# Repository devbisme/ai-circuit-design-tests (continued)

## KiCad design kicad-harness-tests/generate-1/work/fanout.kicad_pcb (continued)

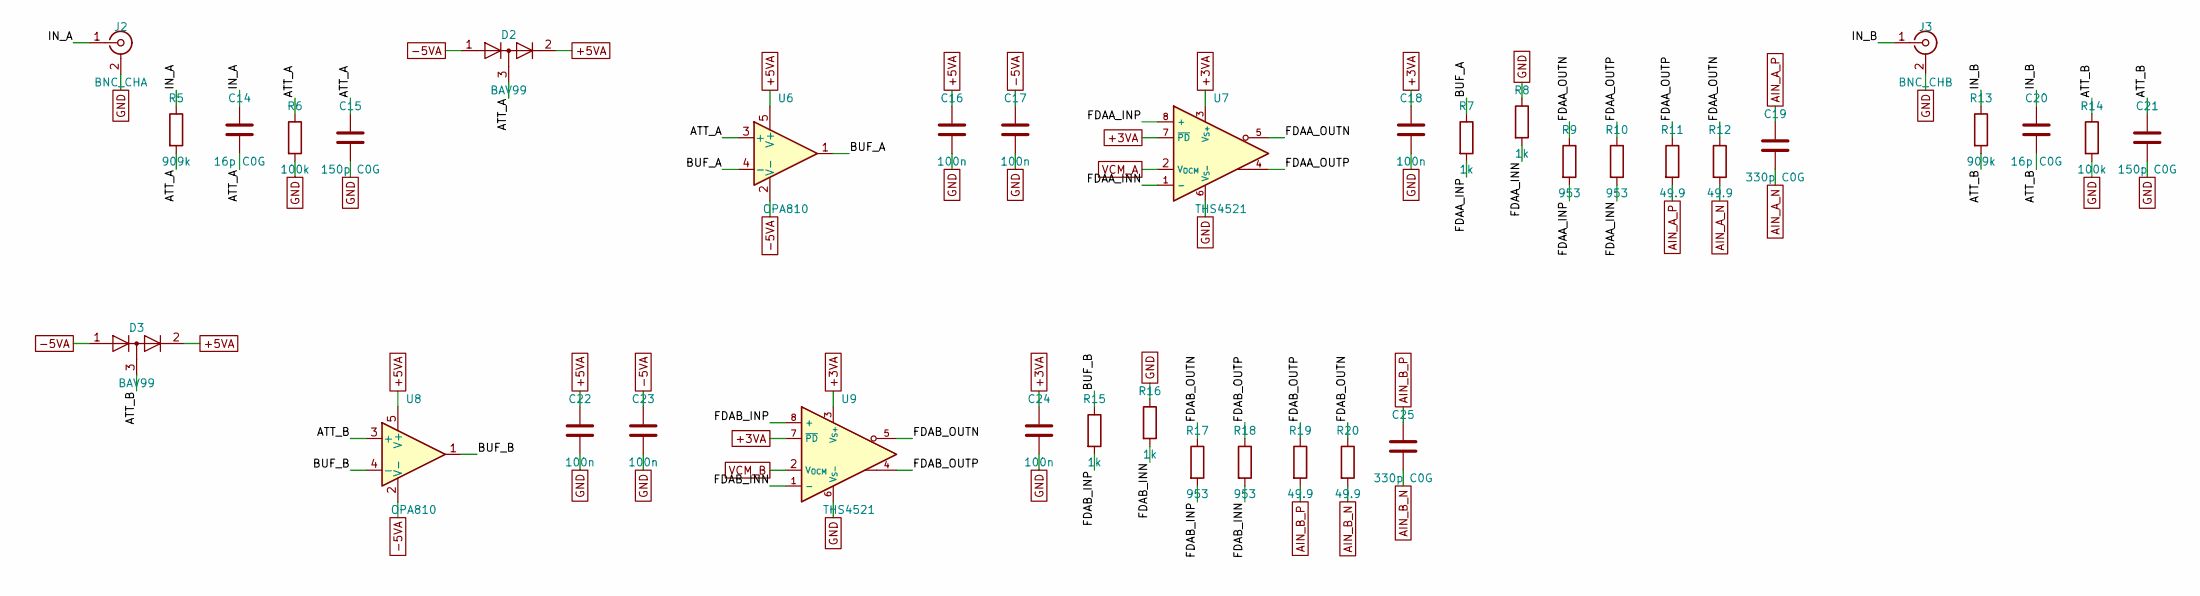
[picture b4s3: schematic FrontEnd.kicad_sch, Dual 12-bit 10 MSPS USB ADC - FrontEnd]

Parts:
C14, C20: 16p C0G; C_1206_3216Metric
C15, C21: 150p C0G; C_0603_1608Metric
C16, C17, C18, C22, C23, C24: 100n; C_0603_1608Metric
C19, C25: 330p C0G; C_0603_1608Metric
D2, D3: BAV99; SOT-23
J2: BNC_CHA; BNC_Amphenol_B6252HB-NPP3G-50_Horizontal
J3: BNC_CHB; BNC_Amphenol_B6252HB-NPP3G-50_Horizontal
R5, R13: 909k; R_1206_3216Metric
R6, R14: 100k; R_0603_1608Metric
R7, R8, R15, R16: 1k; R_0603_1608Metric
R9, R10, R17, R18: 953; R_0603_1608Metric
R11, R12, R19, R20: 49.9; R_0603_1608Metric
U6, U8: OPA810; SOT-23-5
U7, U9: THS4521; SOIC-8_3.9x4.9mm_P1.27mm

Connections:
+3VA: C18.1, C24.1, U7.3 (V_{S+}), U7.7 (~PD), U9.3 (V_{S+}), U9.7 (~PD); also elsewhere on the board
+5VA: C16.1, C22.1, D2.2 (A), D3.2 (A), U6.5 (V+), U8.5 (V+); also elsewhere on the board
-5VA: C17.1, C23.1, D2.1 (K), D3.1 (K), U6.2 (V-), U8.2 (V-); also elsewhere on the board
/FrontEnd/ATT_A: C14.2, C15.1, D2.3 (K), R5.2, R6.1, U6.3 (+)
/FrontEnd/ATT_B: C20.2, C21.1, D3.3 (K), R13.2, R14.1, U8.3 (+)
/FrontEnd/BUF_A: R7.1, U6.1, U6.4 (-)
/FrontEnd/BUF_B: R15.1, U8.1, U8.4 (-)
/FrontEnd/FDAA_INN: R8.2, R10.2, U7.1 (-)
/FrontEnd/FDAA_INP: R7.2, R9.2, U7.8 (+)
/FrontEnd/FDAA_OUTN: R9.1, R12.1, U7.5
/FrontEnd/FDAA_OUTP: R10.1, R11.1, U7.4
/FrontEnd/FDAB_INN: R16.2, R18.2, U9.1 (-)
/FrontEnd/FDAB_INP: R15.2, R17.2, U9.8 (+)
/FrontEnd/FDAB_OUTN: R17.1, R20.1, U9.5
/FrontEnd/FDAB_OUTP: R18.1, R19.1, U9.4
/FrontEnd/IN_A: C14.1, J2.1 (In), R5.1
/FrontEnd/IN_B: C20.1, J3.1 (In), R13.1
AIN_A_N: C19.2, R12.2; also elsewhere on the board
AIN_A_P: C19.1, R11.2; also elsewhere on the board
AIN_B_N: C25.2, R20.2; also elsewhere on the board
AIN_B_P: C25.1, R19.2; also elsewhere on the board
GND: C15.2, C16.2, C17.2, C18.2, C21.2, C22.2, C23.2, C24.2, J2.2 (Ext), J3.2 (Ext), R6.2, R8.1, R14.2, R16.1, U7.6 (V_{S-}), U9.6 (V_{S-}); also elsewhere on the board
VCM_A: U7.2 (V_{OCM}); also elsewhere on the board
VCM_B: U9.2 (V_{OCM}); also elsewhere on the board

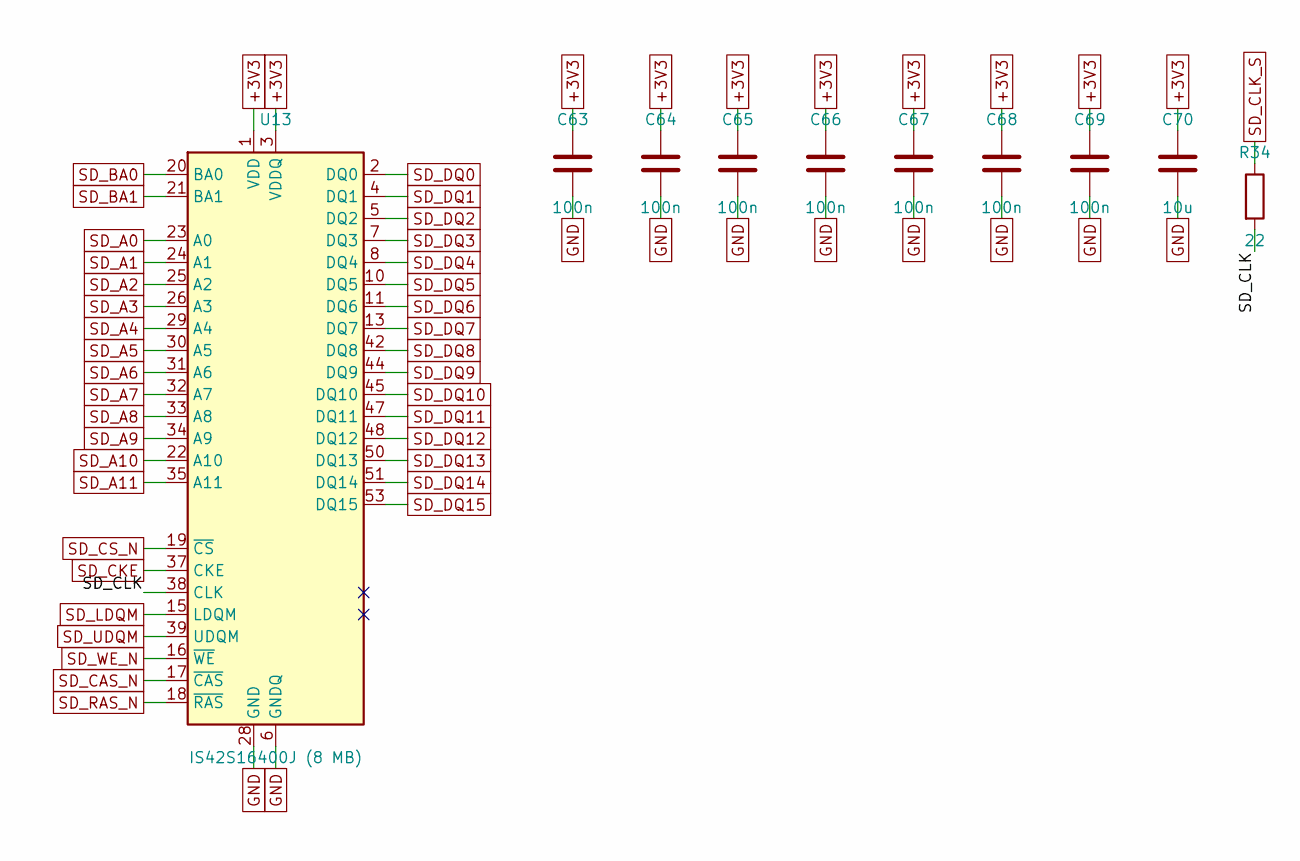
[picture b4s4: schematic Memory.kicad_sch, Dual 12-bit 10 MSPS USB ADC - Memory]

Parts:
C63, C64, C65, C66, C67, C68, C69: 100n; C_0603_1608Metric
C70: 10u; C_0805_2012Metric
R34: 22; R_0603_1608Metric
U13: IS42S16400J (8 MB); TSOP-II-54_22.2x10.16mm_P0.8mm

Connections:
+3V3: C63.1, C64.1, C65.1, C66.1, C67.1, C68.1, C69.1, C70.1, U13.1 (VDD), U13.3 (VDDQ), U13.9 (VDDQ), U13.14 (VDD), U13.27 (VDD), U13.43 (VDDQ), U13.49 (VDDQ); also elsewhere on the board
/Memory/SD_CLK: R34.2, U13.38 (CLK)
GND: C63.2, C64.2, C65.2, C66.2, C67.2, C68.2, C69.2, C70.2, U13.6 (GNDQ), U13.12 (GNDQ), U13.28 (GND), U13.41 (GND), U13.46 (GNDQ), U13.52 (GNDQ), U13.54 (GND); also elsewhere on the board
SD_A0: U13.23 (A0); also elsewhere on the board
SD_A1: U13.24 (A1); also elsewhere on the board
SD_A2: U13.25 (A2); also elsewhere on the board
SD_A3: U13.26 (A3); also elsewhere on the board
SD_A4: U13.29 (A4); also elsewhere on the board
SD_A5: U13.30 (A5); also elsewhere on the board
SD_A6: U13.31 (A6); also elsewhere on the board
SD_A7: U13.32 (A7); also elsewhere on the board
SD_A8: U13.33 (A8); also elsewhere on the board
SD_A9: U13.34 (A9); also elsewhere on the board
SD_A10: U13.22 (A10); also elsewhere on the board
SD_A11: U13.35 (A11); also elsewhere on the board
SD_BA0: U13.20 (BA0); also elsewhere on the board
SD_BA1: U13.21 (BA1); also elsewhere on the board
SD_CAS_N: U13.17 (~CAS); also elsewhere on the board
SD_CKE: U13.37 (CKE); also elsewhere on the board
SD_CLK_S: R34.1; also elsewhere on the board
SD_CS_N: U13.19 (~CS); also elsewhere on the board
SD_DQ0: U13.2 (DQ0); also elsewhere on the board
SD_DQ1: U13.4 (DQ1); also elsewhere on the board
SD_DQ2: U13.5 (DQ2); also elsewhere on the board
SD_DQ3: U13.7 (DQ3); also elsewhere on the board
SD_DQ4: U13.8 (DQ4); also elsewhere on the board
SD_DQ5: U13.10 (DQ5); also elsewhere on the board
SD_DQ6: U13.11 (DQ6); also elsewhere on the board
SD_DQ7: U13.13 (DQ7); also elsewhere on the board
SD_DQ8: U13.42 (DQ8); also elsewhere on the board
SD_DQ9: U13.44 (DQ9); also elsewhere on the board
SD_DQ10: U13.45 (DQ10); also elsewhere on the board
SD_DQ11: U13.47 (DQ11); also elsewhere on the board
SD_DQ12: U13.48 (DQ12); also elsewhere on the board
SD_DQ13: U13.50 (DQ13); also elsewhere on the board
SD_DQ14: U13.51 (DQ14); also elsewhere on the board
SD_DQ15: U13.53 (DQ15); also elsewhere on the board
SD_LDQM: U13.15 (LDQM); also elsewhere on the board
SD_RAS_N: U13.18 (~RAS); also elsewhere on the board
SD_UDQM: U13.39 (UDQM); also elsewhere on the board
SD_WE_N: U13.16 (~WE); also elsewhere on the board

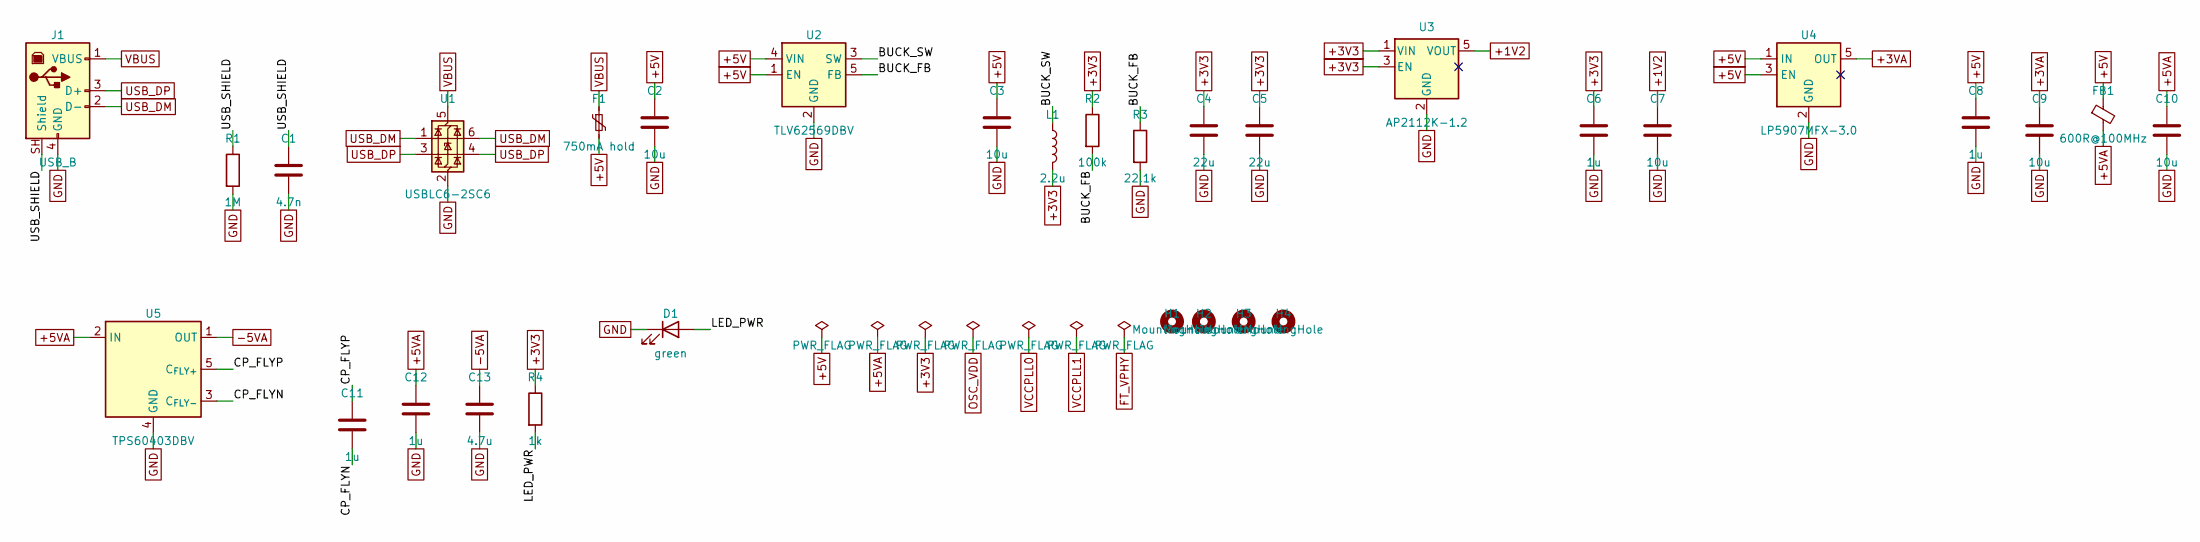
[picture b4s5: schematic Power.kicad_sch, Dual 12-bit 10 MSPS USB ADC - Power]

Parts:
C1: 4.7n; C_0805_2012Metric
C2, C3, C7, C9, C10: 10u; C_0805_2012Metric
C4, C5: 22u; C_0805_2012Metric
C6, C8, C11, C12: 1u; C_0603_1608Metric
C13: 4.7u; C_0805_2012Metric
D1: green; LED_0603_1608Metric
F1: 750mA hold; Fuse_1206_3216Metric
FB1: 600R@100MHz; L_0805_2012Metric
H1, H2, H3, H4: MountingHole; MountingHole_3.2mm_M3
J1: USB_B; USB_B_OST_USB-B1HSxx_Horizontal
L1: 2.2u; L_Bourns-SRN4018
R1: 1M; R_0603_1608Metric
R2: 100k; R_0603_1608Metric
R3: 22.1k; R_0603_1608Metric
R4: 1k; R_0603_1608Metric
U1: USBLC6-2SC6; SOT-23-6
U2: TLV62569DBV; SOT-23-5
U3: AP2112K-1.2; SOT-23-5
U4: LP5907MFX-3.0; SOT-23-5
U5: TPS60403DBV; SOT-23-5

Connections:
+1V2: C7.1, U3.5 (VOUT); also elsewhere on the board
+3V3: C4.1, C5.1, C6.1, L1.2, R2.1, R4.1, U3.1 (VIN), U3.3 (EN); also elsewhere on the board
+3VA: C9.1, U4.5 (OUT); also elsewhere on the board
+5V: C2.1, C3.1, C8.1, F1.2, FB1.1, U2.1 (EN), U2.4 (VIN), U4.1 (IN), U4.3 (EN)
+5VA: C10.1, C12.1, FB1.2, U5.2 (IN); also elsewhere on the board
-5VA: C13.1, U5.1 (OUT); also elsewhere on the board
/Power/BUCK_FB: R2.2, R3.1, U2.5 (FB)
/Power/BUCK_SW: L1.1, U2.3 (SW)
/Power/CP_FLYN: C11.2, U5.3 (C_{FLY-})
/Power/CP_FLYP: C11.1, U5.5 (C_{FLY+})
/Power/LED_PWR: D1.2 (A), R4.2
/Power/USB_SHIELD: C1.1, J1.SH (Shield), R1.1
GND: C1.2, C2.2, C3.2, C4.2, C5.2, C6.2, C7.2, C8.2, C9.2, C10.2, C12.2, C13.2, D1.1 (K), J1.4 (GND), R1.2, R3.2, U1.2 (GND), U2.2 (GND), U3.2 (GND), U4.2 (GND), U5.4 (GND); also elsewhere on the board
USB_DM: J1.2 (D-), U1.1 (I/O1), U1.6 (I/O1); also elsewhere on the board
USB_DP: J1.3 (D+), U1.3 (I/O2), U1.4 (I/O2); also elsewhere on the board
VBUS: F1.1, J1.1 (VBUS), U1.5 (VBUS)

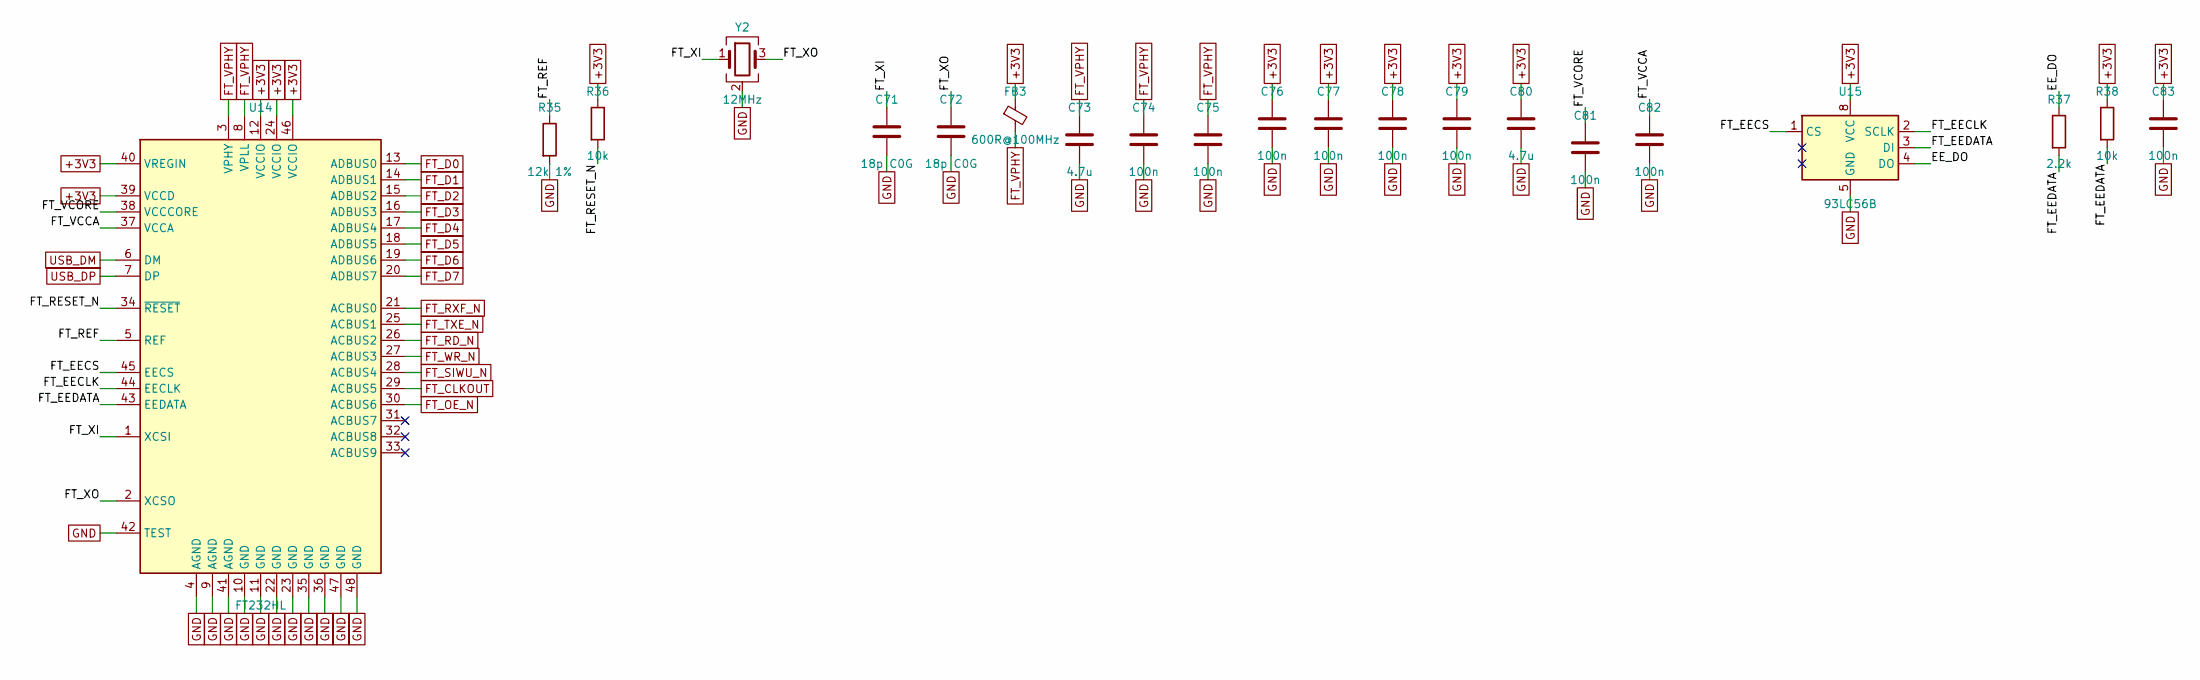
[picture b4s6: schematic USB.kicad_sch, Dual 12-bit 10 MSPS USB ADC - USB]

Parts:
C71, C72: 18p C0G; C_0603_1608Metric
C73, C80: 4.7u; C_0805_2012Metric
C74, C75, C76, C77, C78, C79, C81, C82, C83: 100n; C_0603_1608Metric
FB3: 600R@100MHz; L_0805_2012Metric
R35: 12k 1%; R_0603_1608Metric
R36, R38: 10k; R_0603_1608Metric
R37: 2.2k; R_0603_1608Metric
U14: FT232HL; LQFP-48_7x7mm_P0.5mm
U15: 93LC56B; SOIC-8_3.9x4.9mm_P1.27mm
Y2: 12MHz; Crystal_SMD_3225-4Pin_3.2x2.5mm

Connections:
+3V3: C76.1, C77.1, C78.1, C79.1, C80.1, C83.1, FB3.1, R36.1, R38.1, U14.12 (VCCIO), U14.24 (VCCIO), U14.39 (VCCD), U14.40 (VREGIN), U14.46 (VCCIO), U15.8 (VCC); also elsewhere on the board
/USB/EE_DO: R37.1, U15.4 (DO)
/USB/FT_EECLK: U14.44 (EECLK), U15.2 (SCLK)
/USB/FT_EECS: U14.45 (EECS), U15.1 (CS)
/USB/FT_EEDATA: R37.2, R38.2, U14.43 (EEDATA), U15.3 (DI)
/USB/FT_REF: R35.1, U14.5 (REF)
/USB/FT_RESET_N: R36.2, U14.34 (~RESET)
/USB/FT_VCCA: C82.1, U14.37 (VCCA)
/USB/FT_VCORE: C81.1, U14.38 (VCCCORE)
/USB/FT_XI: C71.1, U14.1 (XCSI), Y2.1
/USB/FT_XO: C72.1, U14.2 (XCSO), Y2.3
FT_CLKOUT: U14.29 (ACBUS5); also elsewhere on the board
FT_D0: U14.13 (ADBUS0); also elsewhere on the board
FT_D1: U14.14 (ADBUS1); also elsewhere on the board
FT_D2: U14.15 (ADBUS2); also elsewhere on the board
FT_D3: U14.16 (ADBUS3); also elsewhere on the board
FT_D4: U14.17 (ADBUS4); also elsewhere on the board
FT_D5: U14.18 (ADBUS5); also elsewhere on the board
FT_D6: U14.19 (ADBUS6); also elsewhere on the board
FT_D7: U14.20 (ADBUS7); also elsewhere on the board
FT_OE_N: U14.30 (ACBUS6); also elsewhere on the board
FT_RD_N: U14.26 (ACBUS2); also elsewhere on the board
FT_RXF_N: U14.21 (ACBUS0); also elsewhere on the board
FT_SIWU_N: U14.28 (ACBUS4); also elsewhere on the board
FT_TXE_N: U14.25 (ACBUS1); also elsewhere on the board
FT_VPHY: C73.1, C74.1, C75.1, FB3.2, U14.3 (VPHY), U14.8 (VPLL)
FT_WR_N: U14.27 (ACBUS3); also elsewhere on the board
GND: C71.2, C72.2, C73.2, C74.2, C75.2, C76.2, C77.2, C78.2, C79.2, C80.2, C81.2, C82.2, C83.2, R35.2, U14.4 (AGND), U14.9 (AGND), U14.10 (GND), U14.11 (GND), U14.22 (GND), U14.23 (GND), U14.35 (GND), U14.36 (GND), U14.41 (AGND), U14.42 (TEST), U14.47 (GND), U14.48 (GND), U15.5 (GND), Y2.2 (G), Y2.4 (G); also elsewhere on the board
USB_DM: U14.6 (DM); also elsewhere on the board
USB_DP: U14.7 (DP); also elsewhere on the board

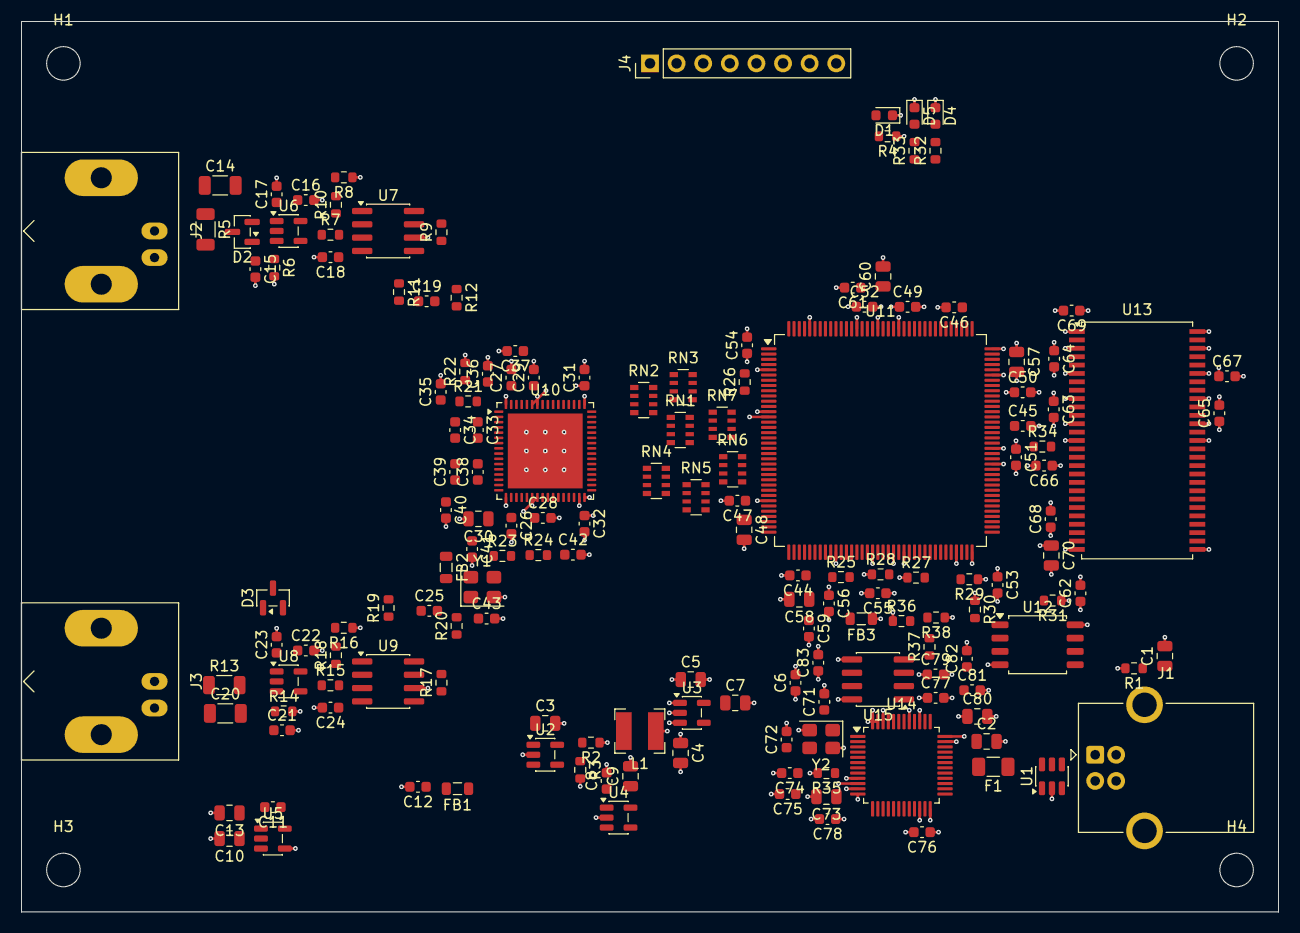
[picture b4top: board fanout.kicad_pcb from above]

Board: 4 copper layers, 120.0 x 85.0 mm, 163 parts (0 on the bottom side), 176 nets.
